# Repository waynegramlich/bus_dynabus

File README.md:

# Bus DynaBus

The Bus DynaBus module is used to control servos and any
other devices that conform to the Robotis<Sup>&reg;</Sub>
Dynamixel<Sup>&reg;</Sub>.  This module supports both
the TTL (3-pin) and RS-485 (4-pin) bus connectors.

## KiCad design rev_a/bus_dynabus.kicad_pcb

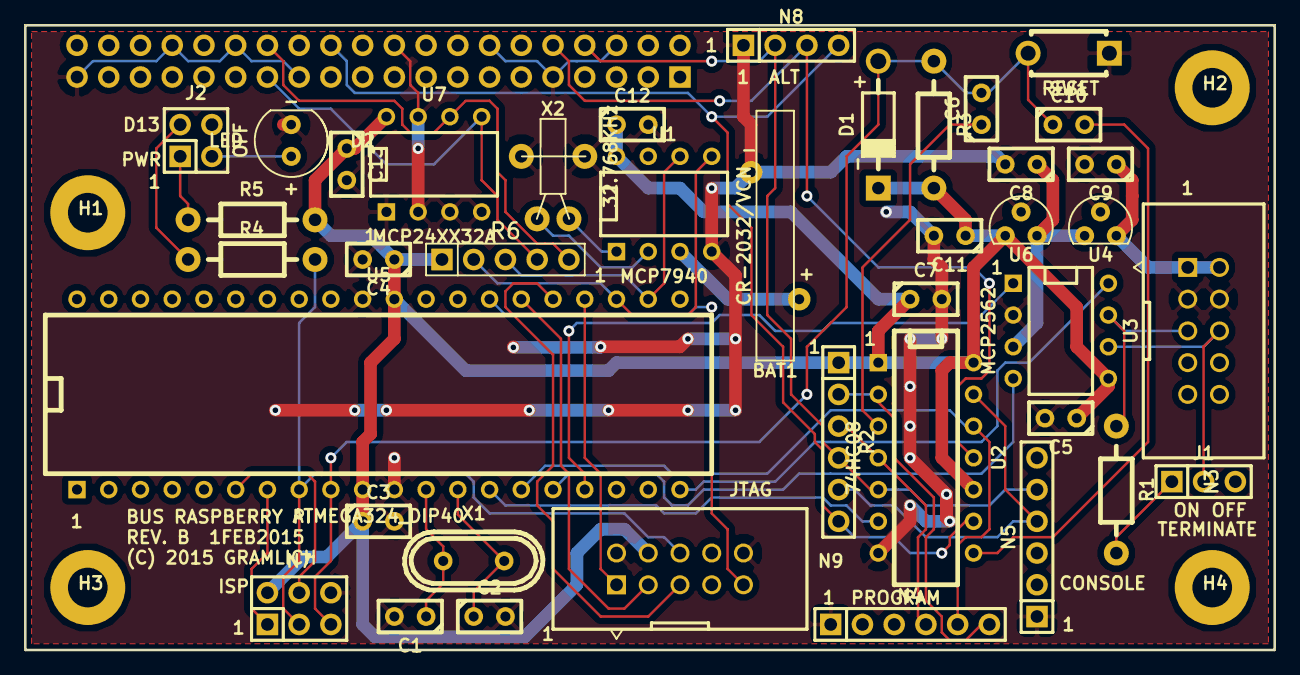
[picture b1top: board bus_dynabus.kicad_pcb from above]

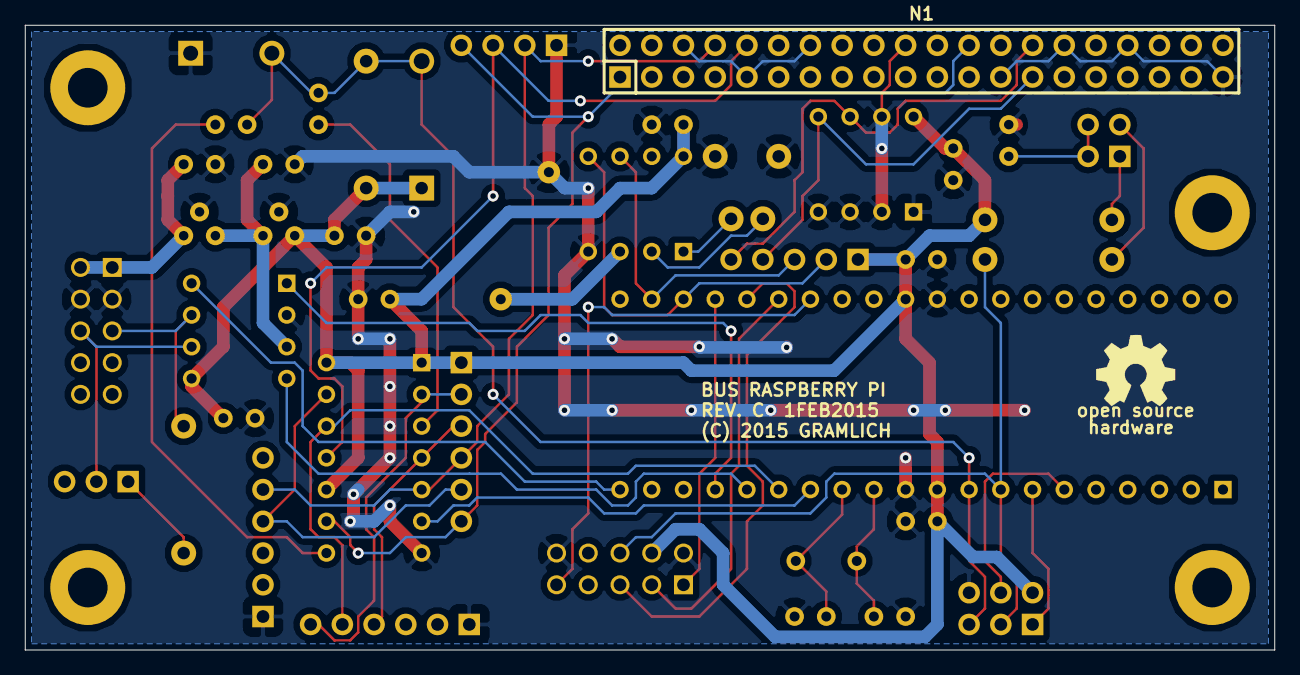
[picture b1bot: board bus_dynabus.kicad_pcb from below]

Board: 2 copper layers, 100.0 x 50.0 mm, 46 parts (2 on the bottom side), 40 nets.

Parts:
BAT1: CR-2032/VCN; 10MM_BATTERY
C1, C2: 18pF; Capacitor3MMDiscRM2.5
C3, C4, C5, C6, C7, C10, C11, C12, C13: .1uF; Capacitor3MMDiscRM2.5
C8, C9: 1uF; Capacitor3MMDiscRM2.5
D1: SD101C-TR; Diode_DO-41_SOD81_Horizontal_RM10
D2: LED; T1_LED
H1, H2, H3, H4: 3MM_HOLE; MountingHole_3mm
H5: OSHW_LOGO; OSHW_LOGO_250mil
J1: TERMINATE_JUMPER; Pin_Header_Straight_1x03
J2: LED_JUMPER; Pin_Header_Straight_2x02
N1: RASPI_CONNECTOR_40; Pin_Header_Straight_2x20
N3: BUS_HEADER; Pin_Header_Straight_2x05_Shrouded
N4, N5: FTDI_HEADER; Pin_Header_Straight_1x06
N7: AVR_ISP_HEADER; Pin_Header_Straight_2x03
N8: SERIAL_CONNECTOR; Pin_Header_Straight_1x04
N9: JTAG_HEADER; Pin_Header_Straight_2x05_Shrouded
R1: 120 1%; Resistor_Horizontal__400
R2: 100K_SIP6; Pin_Header_Straight_1x06
R3: 10K; Resistor_Horizontal__400
R4, R5: 470; Resistor_Horizontal__400
R6: 3K9_SIP5; Pin_Header_Straight_1x05
SW1: MJTP1243; Button_6.5MM
U1: MCP7940; DIP-8__300
U2: 74HC08; DIP-14__300
U3: MCP2562; DIP-8__300
U4: L78L05AC; TO92_123
U5: ATMEGA324_DIP40; DIP-40__600
U6: L78L33AC; TO92_123
U7: MCP24XX32A; DIP-8__300
X1: 16MHz; Crystal_HC49-U_Vertical
X2: 32.768KHz; RTC_CRYSTAL

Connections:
+3.3V: C3.1, C4.1, C5.1, C7.1, C11.1, C12.1, C13.1, D1.-, N7.2, N9.4, R2.1, R3.2, R5.2, R6.1, U1.8, U2.1, U2.10, U2.14, U3.5, U5.10, U5.30, U6.1, U7.8
+5V: C8.1, U3.3, U4.1, U6.3
/BAT: BAT1.+, U1.3
/CANH: N3.5, R1.1, U3.7
/CANL: J1.2, N3.6, U3.6
/LPWR: C9.1, N3.1, N3.2, U4.3
/MISO: N7.1, U5.7
/MOSI: N7.4, U5.6
/RXD0: U2.6, U5.14
/RXD1: U3.4, U5.16
/SCK: N7.3, N9.6, R4.2, U5.8
/TCK: N9.1, U5.24
/TDI: N9.9, U5.27
/TDO: N9.3, U5.26
/TMS: N9.5, U5.25
/TXD0: N4.5, U2.12, U5.15
/TXD1: U3.1, U5.17
/XTAL1: C2.1, U5.13, X1.2
/XTAL2: C1.1, U5.12, X1.1
/~RESET: C6.2, C10.1, D1.+, N7.5, R3.1, SW1.2, U5.9
GND: BAT1.-, C1.2, C2.2, C3.2, C4.2, C5.2, C7.2, C8.2, C9.2, C11.2, C12.2, C13.2, D2.-, N1.6, N1.9, N1.14, N1.20, N1.25, N1.30, N1.34, N1.39, N3.3, N3.4, N4.1, N5.1, N7.6, N8.1, N9.2, N9.10, SW1.1, U1.4, U2.7, U3.2, U4.2, U5.11, U5.31, U6.2, U7.1, U7.2, U7.3, U7.4, U7.7, X2.3, X2.4
unnamed: C6.1, U2.3
unnamed: C10.2, U2.8
unnamed: D2.+, J2.3, J2.4
unnamed: J1.1, R1.2
unnamed: J2.1, R5.1
unnamed: J2.2, R4.1
unnamed: N1.8, N5.5, N8.2, R2.4, U2.5
unnamed: N1.10, N8.3, U2.11
unnamed: N1.24, N8.4, R2.6, U2.9
unnamed: N1.27, R6.4, U7.5
unnamed: N1.28, R6.5, U7.6
unnamed: N4.4, R2.3, U2.4
unnamed: N4.6, R2.2, U2.2
unnamed: N5.4, R2.5, U2.13
unnamed: R6.2, U1.5, U5.23
unnamed: R6.3, U1.6, U5.22
unnamed: U1.1, X2.1
unnamed: U1.2, X2.2
unnamed: U3.8, U5.20

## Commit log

2015-02-03 Made a clone of bus_raspberry_pi Rev. C

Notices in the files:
rev_a/bus_dynabus.kicad_pcb:
(C) 2015 GRAMLICH
